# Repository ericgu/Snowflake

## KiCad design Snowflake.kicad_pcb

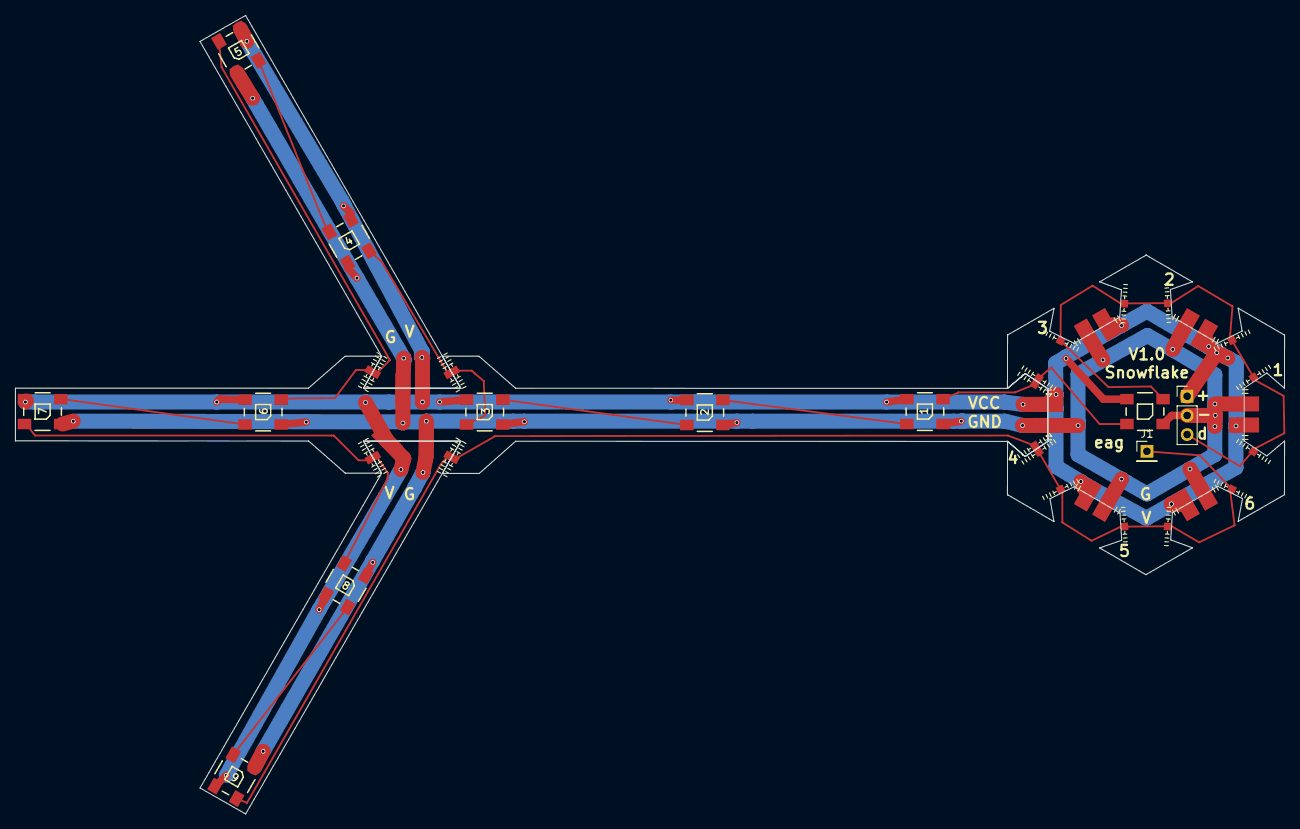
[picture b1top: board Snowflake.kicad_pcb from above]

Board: 2 copper layers, 168.4 x 106.0 mm, 10 parts (0 on the bottom side), 11 nets.

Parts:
1, 2, 3, 4, 5, 6, 7, 8, 9: WS2812B
J1: Pin_Header_Straight_1x01_Pitch2.54mm

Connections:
/DOUT: 9.2, J1.1
/GND: 1.3, 2.3, 3.3, 4.3, 5.3, 6.3, 7.3, 8.3, 9.3
/VCC: 1.1, 2.1, 3.1, 4.1, 5.1, 6.1, 7.1, 8.1, 9.1
unnamed: 4.2, 5.4
unnamed: 3.2, 4.4
unnamed: 2.2, 3.4
unnamed: 1.2, 2.4
unnamed: 7.2, 8.4
unnamed: 6.2, 7.4
unnamed: 8.2, 9.4
unnamed: 5.2, 6.4

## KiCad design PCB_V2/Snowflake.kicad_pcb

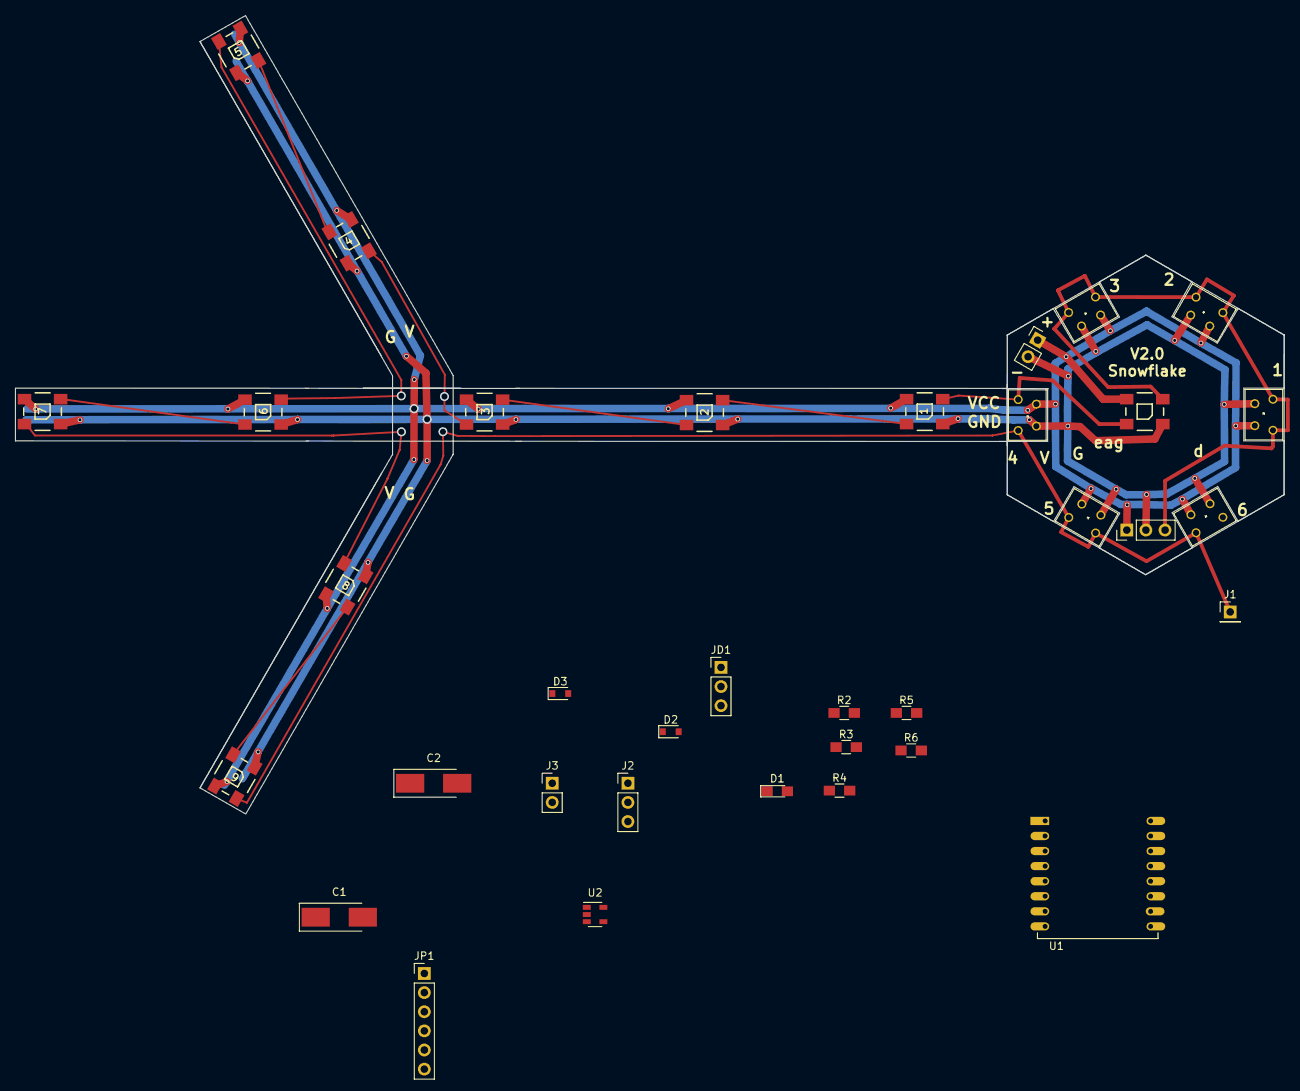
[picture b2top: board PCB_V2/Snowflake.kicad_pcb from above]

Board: 2 copper layers, 168.4 x 106.0 mm, 32 parts (0 on the bottom side), 25 nets.

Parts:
1, 2, 3, 4, 5, 6, 7, 8, 9: WS2812B
C1, C2: 10uF; CP_Tantalum_Case-C_EIA-6032-28_Hand
D1: LED; LED_0805_HandSoldering
D2: 1N4148; D_0805
D3: 1n4148; D_0805
J1, J1#2, J1#3, J1#4, J1#5, J1#6, J1#7: Pin_Header_Straight_1x01_Pitch2.54mm
J2: Conn_01x03; Pin_Header_Straight_1x03_Pitch2.54mm
J3: Pin_Header_Straight_1x02_Pitch2.54mm
JD1: Conn_01x03; Pin_Header_Straight_1x03_Pitch2.54mm
JP1: Conn_01x06; Pin_Header_Straight_1x06_Pitch2.54mm
R2: 1K; R_0805_HandSoldering
R3, R4, R5, R6: 10K; R_0805_HandSoldering
U1: ESP-12
U2: SPX3819M5-L-3-3; SOT-23-5

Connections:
/DIN: J2.3, JD1.3, U1.6
/DOUT: 9.2, J1#7.1
/GND: 1.3, 2.3, 3.3, 4.3, 5.3, 6.3, 7.3, 8.3, 9.3, C1.2, C2.2, J2.2, J3.2, JD1.2, JP1.4, R6.2, U1.9, U2.2
/GPI00: JP1.6, R2.2, U1.12
/RESET: D3.1, JP1.5
/RXD5V: D2.1, JP1.2
/TXD: JP1.1, U1.16
/VC5: C2.1, JD1.1, JP1.3, R3.1, U2.1
/VC33: C1.1, D1.2, R4.1, R5.1, U1.8, U2.5
/VCC: 1.1, 2.1, 3.1, 4.1, 5.1, 6.1, 7.1, 8.1, 9.1, J2.1, J3.1
unnamed: D1.1, R2.1
unnamed: D2.2, U1.15
unnamed: D3.2, U1.1
unnamed: 4.2, 5.4
unnamed: 3.2, 4.4
unnamed: 2.2, 3.4
unnamed: 1.2, 2.4
unnamed: 7.2, 8.4
unnamed: 6.2, 7.4
unnamed: 8.2, 9.4
unnamed: 5.2, 6.4
unnamed: R3.2, U2.3
unnamed: R4.2, U1.3
unnamed: R5.2, U1.11
unnamed: R6.1, U1.10

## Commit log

2017-10-21 initial
2017-10-22 New small pads
2017-10-23 more changes
2017-10-28 panelize
2017-11-22 first translation from C#
2017-12-20 changes, added esp controller
